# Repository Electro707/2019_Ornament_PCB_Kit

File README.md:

# 2019_Ornament_PCB_Kit
A PCB Kit in the shape of an ornament

This repository is archived, as it's a one-time design.
Now files are hosted on Google Drive.

Link to website, in which the Google Drive link can be found:
[Link](https://electro707.com/documentation/PCB/2019_Ornament/index.php)

I may create a new general reposity for the kit that will be updated as time goes on 
(there also won't be any of the University of New Haven logos on that one).

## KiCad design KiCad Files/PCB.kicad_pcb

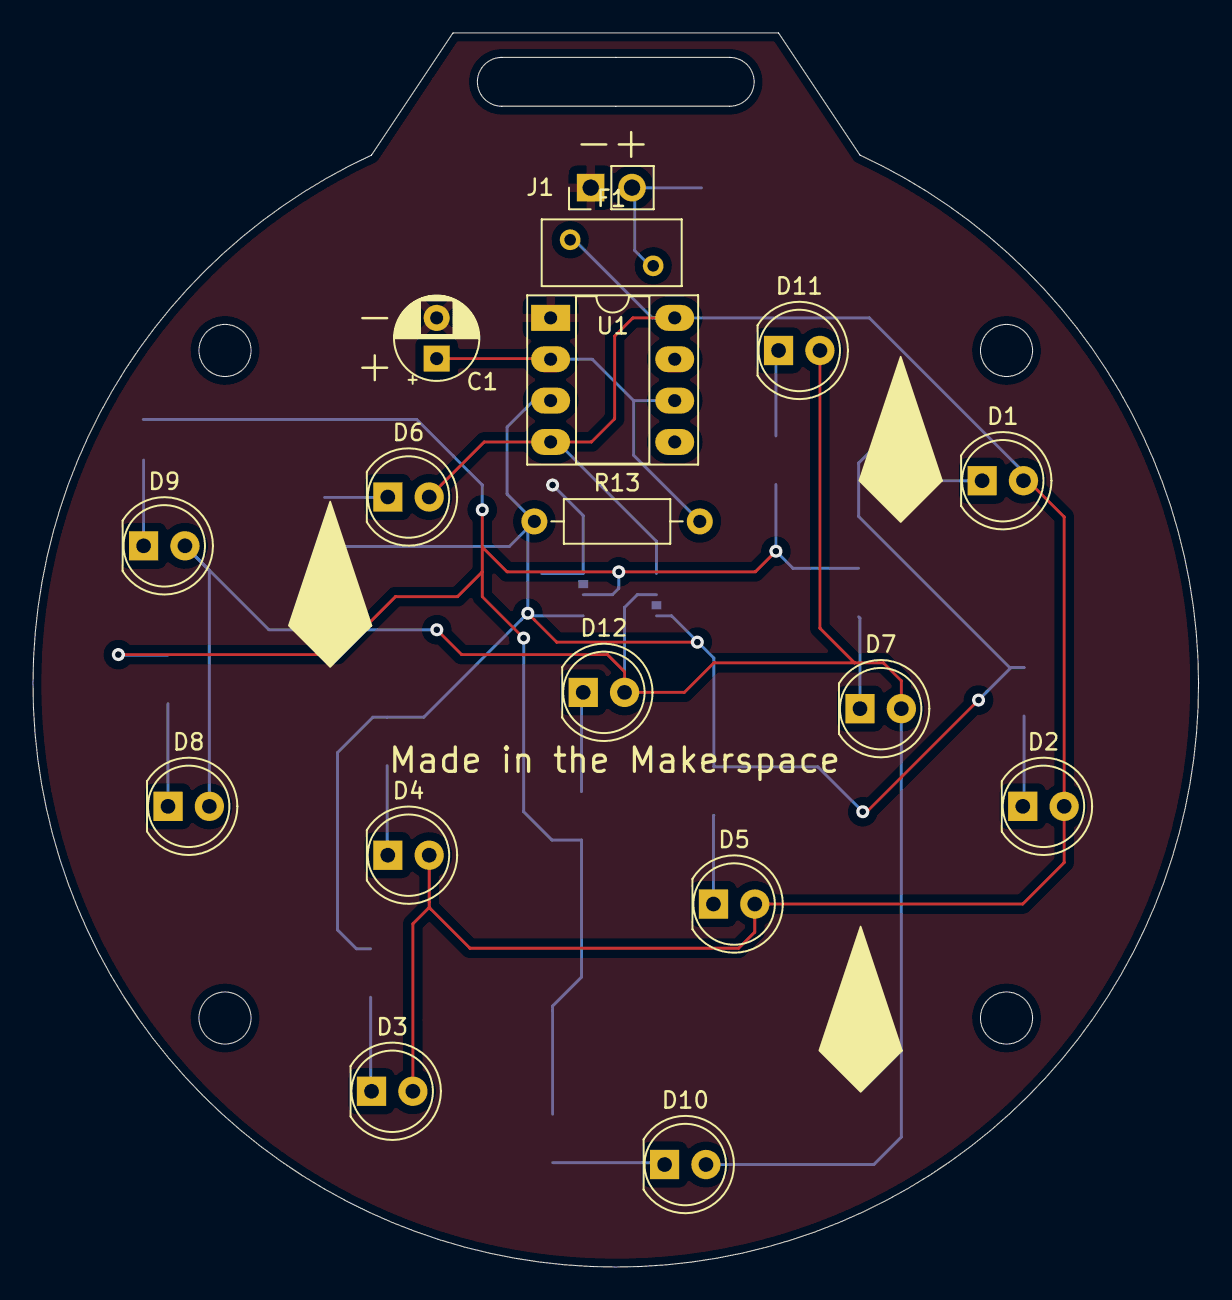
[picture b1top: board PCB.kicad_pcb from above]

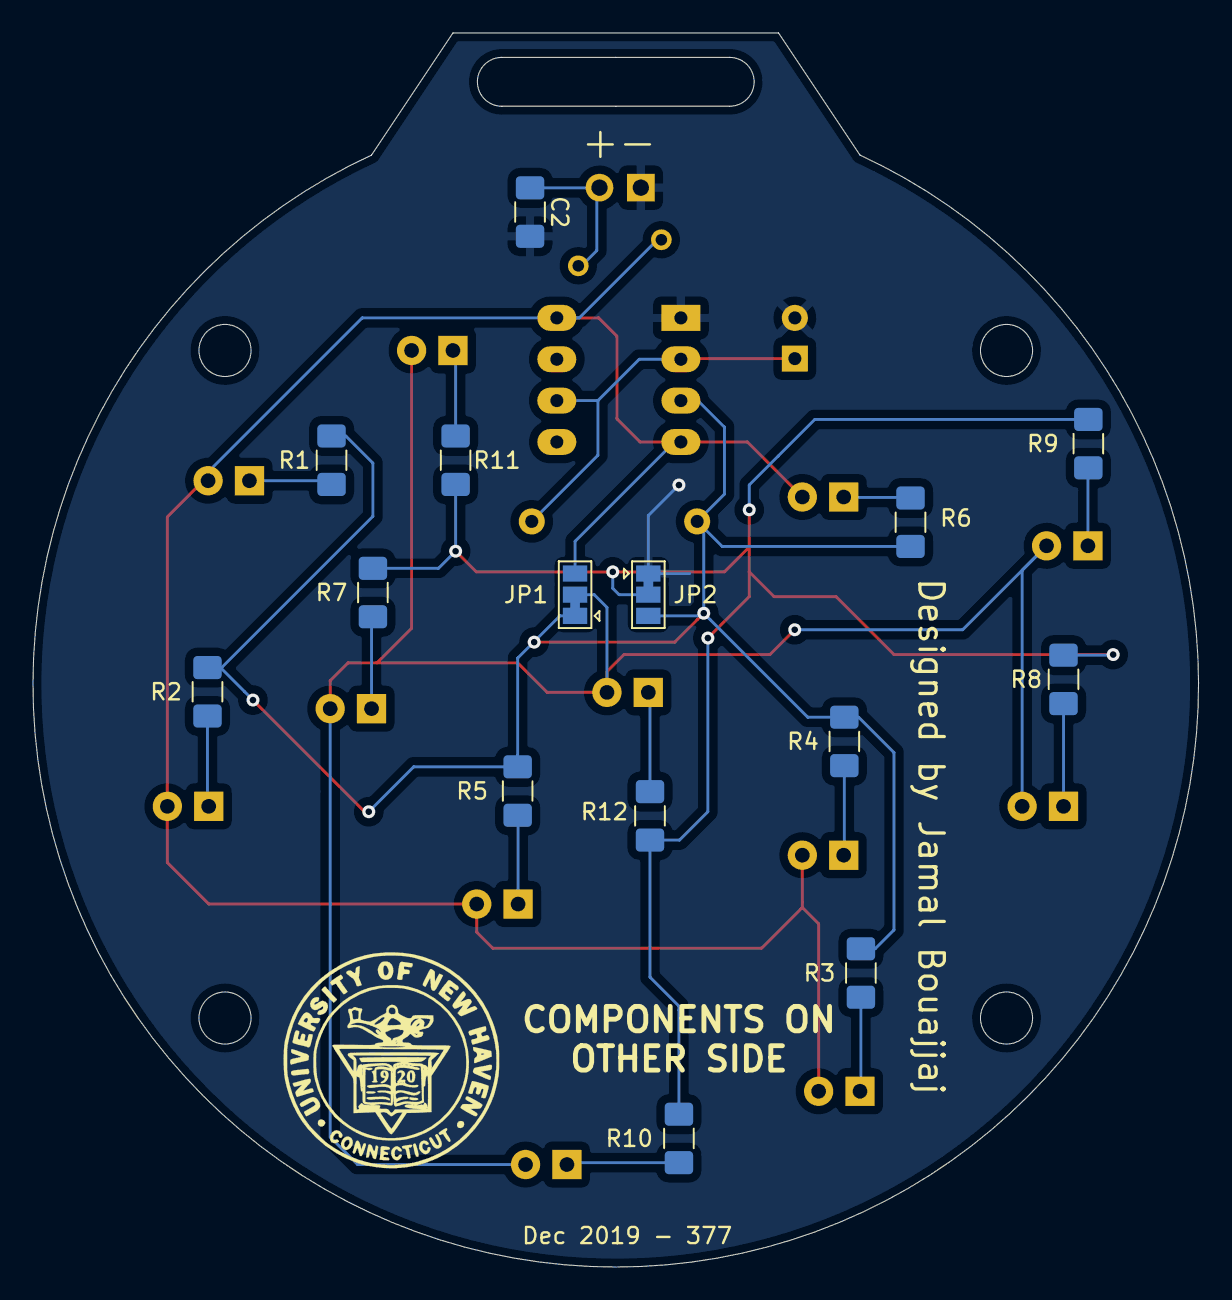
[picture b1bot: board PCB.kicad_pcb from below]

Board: 2 copper layers, 71.6 x 75.8 mm, 36 parts (15 on the bottom side), 19 nets.

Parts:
C1: C; CP_Radial_D5.0mm_P2.50mm
C2: 1uF; C_1206_3216Metric_Pad1.42x1.75mm_HandSolder
D1, D2, D3, D4, D5, D6, D7, D8, D9, D10, D11, D12: LED_ALT; LED_D5.0mm
F1: Polyfuse; Fuse_BelFuse_0ZRE0005FF_L8.3mm_W3.8mm
H1, H2, H3, H4: M3 Mounting Hole; MountingHole_3.2mm_M3_DIN965
J1: Battery; PinHeader_1x02_P2.54mm_Vertical
JP1, JP2: SolderJumper_3_Bridged12; SolderJumper-3_P1.3mm_Bridged12_Pad1.0x1.5mm
R1, R2, R3, R4, R5, R6, R7, R8, R9, R10, R11, R12: 68; R_1206_3216Metric_Pad1.42x1.75mm_HandSolder
R13: R; R_Axial_DIN0207_L6.3mm_D2.5mm_P10.16mm_Horizontal
U1: LM555; DIP-8_W7.62mm_Socket_LongPads

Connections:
GND: C1.2, C2.2, J1.1, JP2.1, U1.1
unnamed: C1.1, R13.2, U1.2, U1.6
unnamed: C2.1, F1.2, J1.2
unnamed: D1.1, R1.1
unnamed: D2.1, R2.1
unnamed: D3.1, R3.1
unnamed: D4.1, R4.1
unnamed: D5.1, R5.1
unnamed: D6.1, R6.1
unnamed: D7.1, R7.1
unnamed: D8.1, R8.1
unnamed: D9.1, R9.1
unnamed: D10.1, R10.1
unnamed: D7.2, D8.2, D9.2, D10.2, D11.2, D12.2, JP1.2
unnamed: D11.1, R11.1
unnamed: D12.1, R12.1
unnamed: JP1.1, JP2.3, R1.2, R2.2, R3.2, R4.2, R5.2, R6.2, R13.1, U1.3
unnamed: JP2.2, R7.2, R8.2, R9.2, R10.2, R11.2, R12.2
VCC: D1.2, D2.2, D3.2, D4.2, D5.2, D6.2, F1.1, JP1.3, U1.4, U1.8

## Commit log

2020-04-16 Pre-Archive Change
